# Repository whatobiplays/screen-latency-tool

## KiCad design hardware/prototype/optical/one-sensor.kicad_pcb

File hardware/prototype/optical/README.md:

# One-sensor optical manufacturing files

## 1. Purpose and release boundary

For the supervised first prototype use the independent
[noncontact mount and manual display session](bench-mount.md). Its numerical
clearance limit comes from the configuration's tolerance/movement budget, not
a universal glass gap. Contact-boot compression/force is not a requirement for
that variant. Owner fit evidence and exact fabrication authorization remain
necessary. Preserve the existing optical PCB and the retained fabrication ZIP;
current assembly instructions supplement its historical review package.

The [source-bound fabrication reference](fabrication-review.md) compares the
unchanged CAM with the proposed standard two-layer process and records the
J1 hole-tolerance and near-edge legend risks for the owner decision. Nominal
fit is not a guarantee of received-board fit; retain the unpowered inspection.

This workflow prepares provisional files for the existing 50 × 44 mm, two-layer,
nominal 1.6 mm optical evaluation board. It preserves the upright SFH 203,
selected MPNs, footprints, placements, outline, routing, analog values and absence
of mounting holes. It does not export a power/USB carrier PCB.

An export is not a fabrication release. Resolve material package-fit and
manufacturing findings, obtain independent review, then request owner approval
through [Issue #38](https://github.com/whatobiplays/screen-latency-tool/issues/38).
Keep `FABRICATION HOLD` whenever a defensible physical arrangement cannot be
established. Physical optical characterization belongs to
[Issue #7](https://github.com/whatobiplays/screen-latency-tool/issues/7).
Missing historical Gate A inputs are a verification gap, not a demonstrated
stability failure.

## 2. Export from a verified checkout

Use Node.js 22 or newer, KiCad CLI **10.0.8**, and the `zip` command. Run from
the repository root. Set `KICAD_CLI` for a nonstandard installation; the default
is `/Applications/KiCad/KiCad.app/Contents/MacOS/kicad-cli`.

```sh
make check
KICAD_KEEP_REPORTS=1 make check-kicad
node scripts/export-optical-cam.mjs --out-dir /absolute/external/path/run-1
node scripts/export-optical-cam.mjs --out-dir /absolute/external/path/run-2
node scripts/export-optical-cam.mjs --compare /absolute/external/path/run-1 /absolute/external/path/run-2
git diff --check
```

Choose new output directories outside the checkout. Existing destinations are
rejected. A failed run may retain partial files for investigation. The exporter
attempts to remove archives and the checksum sidecar after failure; if the
filesystem refuses removal, it reports those errors alongside the original
failure. Any remaining files are failed artifacts and must not be fabricated.
Do not reuse a failed run's directory for another attempt.
The board hash is pinned to the approved input. A different board requires
design review before deliberately updating that pin.

Each run copies the native projects, required libraries, source BOM and assembly
guides into `review/native`. KiCad performs DRC with schematic parity,
all severities and exclusions, `--refill-zones` and `--save-board` on that
disposable board. A second DRC reads the saved board without refilling it.
Gerbers, drills and reference drawings use that same saved snapshot. The
workflow checks its hash after validation and export and verifies that
authoritative input hashes did not change.

Both schematics receive fresh ERC with error, warning and exclusion reporting.
The five historical DRC ignores and four historical ERC ignores remain visible
in the manifest. A separate diagnostic project enables the five ignored DRC
categories and raises permissive rules to the OSH Park manufacturing floors.
It checks the saved copper without another fill. Its findings require individual
disposition; it does not silently change the source project or confer approval.

## 3. CAM settings and contents

The fabrication ZIP contains only these eight files:

| File | Purpose |
| --- | --- |
| `one-sensor-F_Cu.gbr`, `one-sensor-B_Cu.gbr` | Front and back copper |
| `one-sensor-F_Mask.gbr`, `one-sensor-B_Mask.gbr` | Front and back solder-mask openings |
| `one-sensor-F_Silkscreen.gbr`, `one-sensor-B_Silkscreen.gbr` | Front and back legend; an empty back legend is valid |
| `one-sensor-Edge_Cuts.gbr` | Closed board outline |
| `one-sensor.drl` | Combined Excellon drill file |

Gerbers use X2 and net attributes, millimetres, 4.6 coordinate precision,
absolute origin, no mirroring, no border and no common layers. Mask openings
are subtracted from silk. Drills use millimetres, decimal coordinates,
absolute origin, alternate slot mode and no mirroring. The current design
contains 25 plated vias and nine plated component holes, with no NPTH.
No paste layers or stencil are needed for the selected iron assembly method.
These settings follow [OSH Park's KiCad export guidance](https://docs.oshpark.com/design-tools/kicad/generating-kicad-gerbers/).

`review.zip` contains the manifest, original board, saved export snapshot,
native projects/libraries, complete source BOM, optical-only BOM, assembly
guides, schematic PDF, front/back reference assembly PDFs, placement CSV,
Gerber job file when emitted, commands and native reports. The optical BOM
retains all 23 positions: 17 populated components, R4 DNP and five bare test
pads. Placement CSV is a reference, not a vendor-approved automated assembly
file; inspect its DNP and bare-pad entries before any later use.

`manifest.json` records source commit and dirty state, tool version, input and
saved-board hashes, ignored checks, diagnostic profile, settings and payload
inventory. `SHA256SUMS` covers the manifest and both ZIPs. Preserve the original
files and hashes. Final evidence must identify the clean reviewed commit;
uncommitted exports remain provisional.

## 4. Independent validation and fit

Check actual Gerber and Excellon data with an independent parser and rendered
artwork. Verify layer roles, the outline centreline dimensions, pad and drill
registration, drill tools, copper-edge spacing, annular rings, masks and readable
polarity labels. A stroked outline's bounding box is larger than its routed
centreline; do not mistake the 0.05 mm outline stroke for a board-size change.

Compare repeated exports before accepting the package. The comparison permits
only recognized Gerber/Excellon creation-time fields and comments to differ.
It neither edits the CAM files nor ignores geometry, tool, layer or net changes.
Keep raw hashes for each run; timestamps can prevent byte-identical exports.

Use [OSH Park's two-layer specifications](https://docs.oshpark.com/services/two-layer/)
for actual DFM: 0.1524 mm copper width/spacing, 0.254 mm minimum drill,
0.127 mm annular ring, 0.381 mm copper-to-edge clearance, mask webs and
registration, legend limits and standard construction. Larger existing
clearances stay in force. The public approximately $17.05 three-board estimate
for this outline is not a design-specific quote. No fabricator upload or
preview acceptance is implied.

Complete the dimensioned fit review and
[BENCH-002 assembly and unpowered inspection](../../../docs/bench/PROTOTYPE-BENCH-GUIDE.md#provisional-soldered-implementation).
The boot, detector stand-off, clamp, cable bend/retention, display contact force,
trimmer adjustment and underside lead clearance require evidence beyond a
2D board plot. Keep R4 DNP and CABLE-PH04 black=`3V3`, red=`GND`.
No instructions here authorize assembly, connection or energization.
`INITIAL_CURRENT_LIMIT=UNSET` and all Stage-B/C gates remain unchanged.

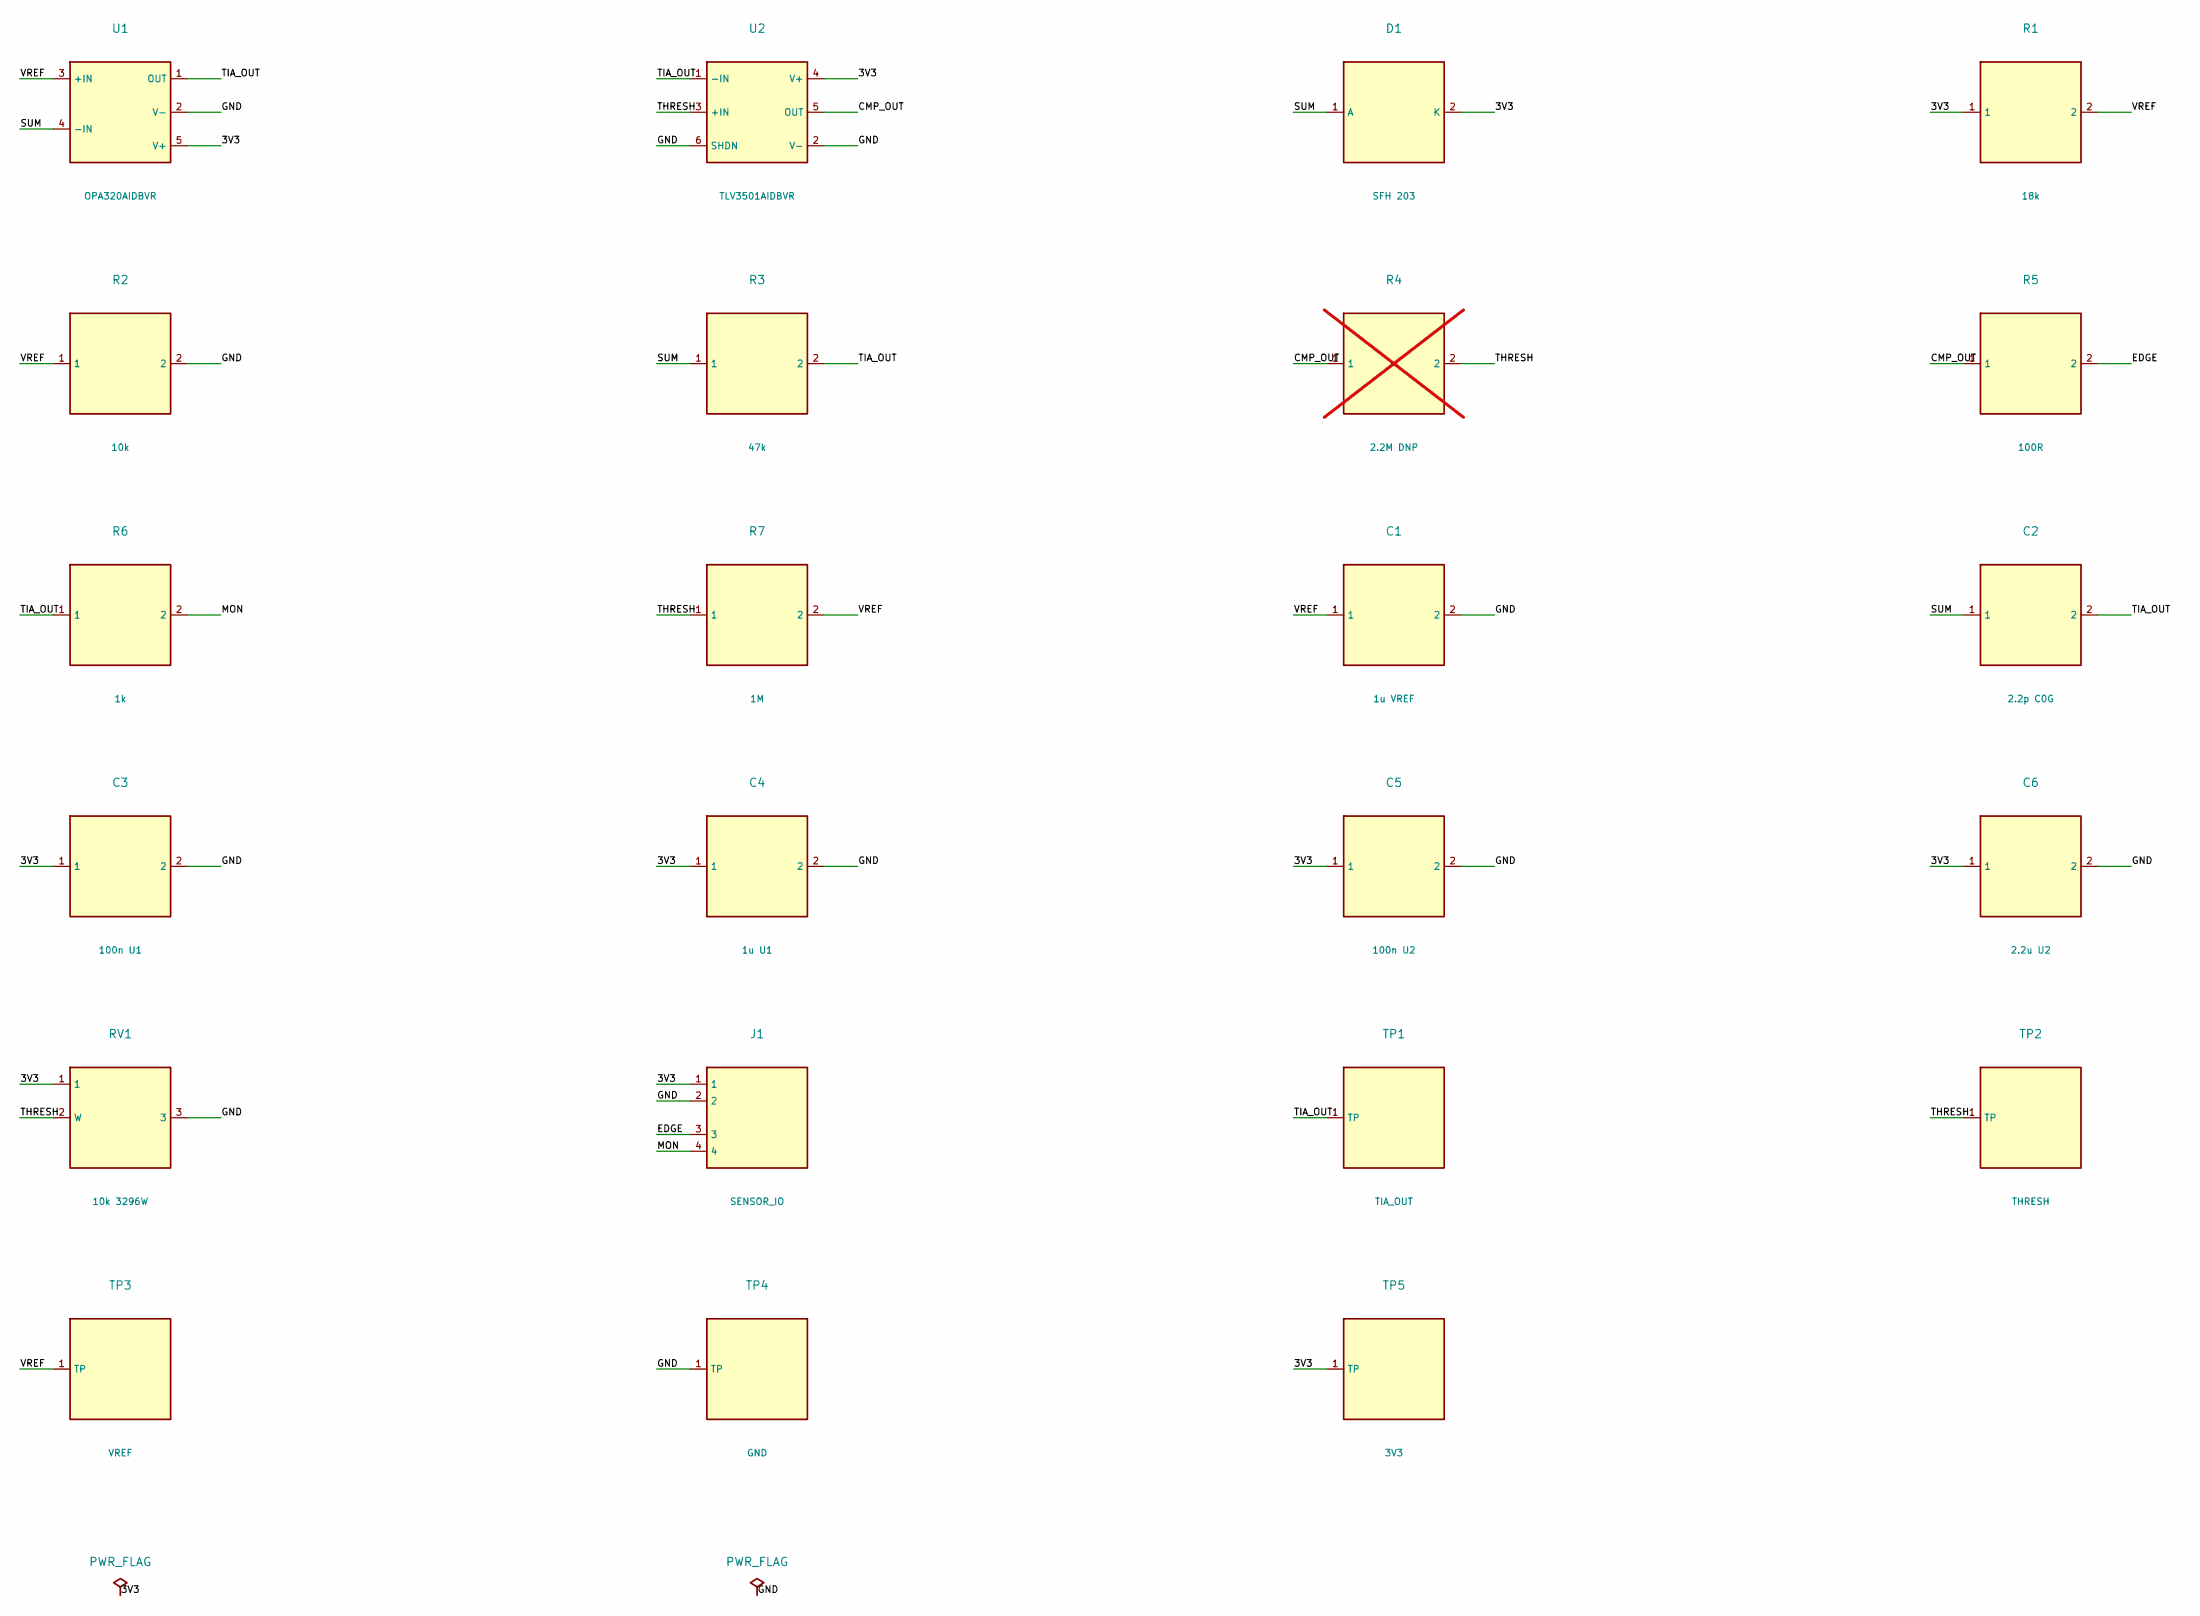
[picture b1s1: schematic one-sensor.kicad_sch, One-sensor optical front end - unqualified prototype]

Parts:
C1: 1u VREF; C_0603_1608Metric; MPN CL10A105KP8NNNC
C2: 2.2p C0G; C_0603_1608Metric; MPN CC0603CRNPO9BN2R2
C3: 100n U1; C_0603_1608Metric; MPN KGM15BR71H104KM
C4: 1u U1; C_0603_1608Metric; MPN CL10A105KP8NNNC
C5: 100n U2; C_0603_1608Metric; MPN KGM15BR71H104KM
C6: 2.2u U2; C_0603_1608Metric; MPN CL10A225KP8NNNC
D1: SFH 203; Photodiode_SFH203; MPN Q62702P0955
J1: SENSOR_IO; JST_PH_B4B-PH-K_1x04_P2.00mm_Vertical; MPN B4B-PH-K-S(LF)(SN)
R1: 18k; R_0603_1608Metric; MPN RC0603FR-0718KL
R2: 10k; R_0603_1608Metric; MPN ERJ-3EKF1002V
R3: 47k; R_0603_1608Metric; MPN RC0603FR-0747KL
R4: 2.2M DNP; R_0603_1608Metric; MPN RC0603FR-072M2L; not fitted
R5: 100R; R_0603_1608Metric; MPN RC0603FR-07100RL
R6: 1k; R_0603_1608Metric; MPN RC0603FR-071KL
R7: 1M; R_0603_1608Metric; MPN RC0603FR-071ML
RV1: 10k 3296W; Potentiometer_Bourns_3296W_Vertical; MPN 3296W-1-103LF
TP1: TIA_OUT; TestPoint_Pad_D1.5mm
TP2: THRESH; TestPoint_Pad_D1.5mm
TP3: VREF; TestPoint_Pad_D1.5mm
TP4: GND; TestPoint_Pad_D1.5mm
TP5: 3V3; TestPoint_Pad_D1.5mm
U1: OPA320AIDBVR; SOT-23-5; MPN OPA320AIDBVR
U2: TLV3501AIDBVR; SOT-23-6; MPN TLV3501AIDBVR

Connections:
/3V3: C3.1, C4.1, C5.1, C6.1, D1.2 (K), J1.1, R1.1, RV1.1, TP5.1, U1.5 (V+), U2.4 (V+)
/CMP_OUT: R4.1, R5.1, U2.5 (OUT)
/EDGE: J1.3, R5.2
/GND: C1.2, C3.2, C4.2, C5.2, C6.2, J1.2, R2.2, RV1.3, TP4.1, U1.2 (V-), U2.2 (V-), U2.6 (SHDN)
/MON: J1.4, R6.2
/SUM: C2.1, D1.1 (A), R3.1, U1.4 (-IN)
/THRESH: R4.2, R7.1, RV1.2 (W), TP2.1, U2.3 (+IN)
/TIA_OUT: C2.2, R3.2, R6.1, TP1.1, U1.1 (OUT), U2.1 (-IN)
/VREF: C1.1, R1.2, R2.1, R7.2, TP3.1, U1.3 (+IN)

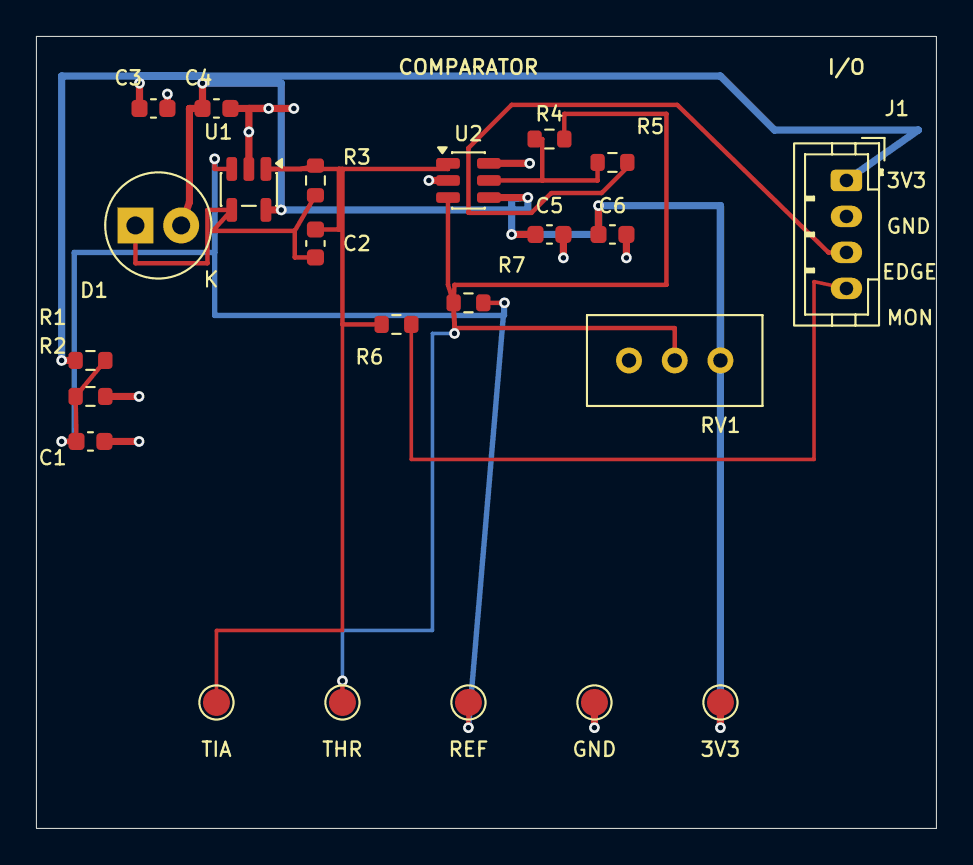
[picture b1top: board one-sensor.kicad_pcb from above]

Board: 2 copper layers, 50.0 x 44.0 mm, 23 parts (0 on the bottom side), 9 nets.
